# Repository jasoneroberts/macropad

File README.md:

# Macropad with a screen

A wireless macropad with MX keys, an EC11 knob and a small LCD that shows what each key does. It is built on the same nRF52840 / Zephyr / nRF Connect SDK stack as the [trackball](https://github.com/jasoneroberts/NordicMouseProject), with a 3D-printed case and a hand-soldered PCB. Started 2026-10-20.

Status 2026-10-21: concept B (12 keys, 2.0″ screen) and the SuperMini nRF52840 controller are chosen. The case model, firmware and PCB inputs exist for all three concepts; the firmware compiles but has not run on hardware yet, and nothing has been printed. Next: buy the screen and an EC11 knob and try the firmware on the nRF52840 DK.

Status 2026-11-11: the concept B main PCB is designed in full (schematic, placement, routing, ground pours) with its parts in a shared JR component library, ready to import into Altium 19 and order from JLCPCB: see `pcb/B/altium/README.md`. The controller pin map changed with it (LCD on footprint pins 5-10, rows 0/1 on P1.15/P0.02); the firmware and case follow.

| | A · Pocket | B · Studio (chosen) | C · Deck |
|---|---|---|---|
| Keys | 3 × 3 MX hot-swap | 4 × 3 MX hot-swap | 4 × 4 MX hot-swap |
| Knob (EC11) | Ø26 | Ø28 | Ø36 |
| Screen | 1.69″ ST7789V2 240 × 280, portrait | 2.0″ ST7789 320 × 240, landscape | 1.28″ GC9A01 240 × 240, round |
| Footprint on desk | 76 × 122 mm | 101 × 118 mm | 92 × 142 mm |
| Height front / rear | 12.5 / 25.1 mm | 12.5 / 24.6 mm | 12.5 / 29.5 mm |
| Tilt | 6° | 6° | 7° |
| LiPo | 603040 | 603040 | 803040 |

Heights are without the 10 mm rubber feet (add about 2 mm).

## Folder

| Path | What |
|---|---|
| `scad/macropad.scad` | The parametric model. Every dimension is a named parameter at the top. |
| `stl/<A,B,C>/print/` | `top`, `bottom`, `knob`, `clamp`, already oriented for the printer bed. |
| `stl/<A,B,C>/view/` | Every part and dummy component (PCB, switches, display, controller, battery) in the assembled position. Made by `tools/build.py`; not kept in git. |
| `stl/test_coupon.stl` | Print this first: switch holes 13.9 / 14.0 / 14.1 / 14.2 (1 to 4 dots) and two insert holes. |
| `dxf/pcb_outline_<c>.dxf` | Main PCB outline with MX centre holes (Ø4) and pillar holes (Ø2.2), for Altium. Plate-frame mm, origin at the case's front-left corner. |
| `build/report_<c>.json` | Dimensions and positions of everything, plus the fit-check result. |
| `build/viewer_<c>.glb` | Coloured assembly. Opens in Windows 3D Viewer. |
| `build/fitcheck.txt` | Overlap check between all parts. Should say `OK` for each concept. |
| `page/index.html` | The concept comparison page with 3D viewers. Made by `tools/make_page.py`; not kept in git. |
| `tools/` | `build.py` (STLs, DXF, report, fit check, GLB), `drawings.py` (plan and section SVGs), `make_page.py` + `page_template.html`, `build_firmware.sh` (Linux: installs NCS v3.3.0 and builds all six firmware variants; CI runs it too). |
| `firmware/` | Zephyr / NCS v3.3.0 app: keys, knob, LVGL screen, USB + Bluetooth HID. See `firmware/README.md`. |
| `firmware/prebuilt/` | Ready-to-flash concept B images: `macropad_B_promicro.uf2` and `macropad_B_dk.hex`. GitHub Actions also builds them on every firmware change (the run's "Artifacts"). |
| `pcb/` | The concept B board for Altium (`pcb/B/altium/`), its KiCad working copy and scripts (`pcb/B/kicad/`, `pcb/board/`), the shared JR component library (`pcb/library/`), and `generate.py`'s starting kits for all three concepts. See `pcb/README.md`. |
| `SHOPPING.md` | What to buy for B (UK prices) and what to measure when it arrives. |
| `LICENSES/` | Upstream licences for the files based on Nordic and Zephyr samples (see "Licences" below). |

## Rebuild after changing a parameter

Needs OpenSCAD 2021.01 or newer, Python 3 and `pip install trimesh manifold3d numpy scipy networkx`.

From the repo root:

```
python tools/build.py          # all concepts (or: build.py B)
python tools/drawings.py
python pcb/generate.py         # needs pip install shapely
python tools/make_page.py page
```

To export one part by hand: `openscad -D 'concept="B"' -D 'part="top_print"' -o top.stl scad/macropad.scad`. Open the file in the OpenSCAD GUI to use the Customizer for `concept` and `part`.

## Measure before printing

These come from listings or datasheets, not from parts on the bench:

- Display glass outline, thickness and where the active area sits on the glass (`LCD169`, `LCD200`, `GC9A01` tables). Board sizes and active areas are from Waveshare; glass outlines are estimates.
- EC11 body height above the PCB (`enc_body_h`, 6.5) and shaft length (`enc_shaft_l`, 15).
- Heat-set insert hole (`insert_d` 4.0, `insert_len` 4.0 for M3 × 4 short inserts).
- LiPo size (`LIPO_603040`, `LIPO_803040`).
- Switch hole (`sw_hole` 14.0): use the test coupon.

## How it's built

- Top shell = switch plate. 3 mm skin: 1.5 mm lip with the 14 mm hole, 15 mm pocket below for the MX clips. PCB top 5.0 mm below the plate top (MX standard), Kailh sockets under the PCB.
- The top surface is tilted, the bottom plate is flat, so the inside gets deeper toward the back. LiPo, controller and display stack live under the rear band.
- Display: window = active area + 0.4 mm with a 45° chamfer through a 1 mm bezel; glass in a pocket; printed clamp with two M2 screws holds the module board. Main PCB has a cut-out there; 8 wires to the module.
- Controller: SuperMini nRF52840 (chosen 2026-10-21; a nice!nano v2 also fits) on 2.5 mm headers under the PCB, component side down, USB-C (mid-mount, centred on the 1.6 mm module board) through a 13 × 7.5 mm rear opening.
- Four M3 countersunk screws into M3 heat-set inserts in the corner bosses; M2 self-tapping screws for the PCB pillars and the display clamp; slide switch slot in the right wall for the OS102011MA1QN1's actuator.
- Prints without supports: top shell face down, bottom plate and clamp flat, knob top face down. Largest part is C's top shell, 92 × 140 mm.

## Licences

No licence has been chosen for the project as a whole yet, so the default applies (all rights reserved). Two kinds of file keep their upstream licence, named by the `SPDX-License-Identifier` line at the top of the file:

- `firmware/src/BT.c` is based on Nordic's `peripheral_hids_keyboard` sample: `LicenseRef-Nordic-5-Clause` (`LICENSES/LicenseRef-Nordic-5-Clause.txt`), which allows use only with Nordic chips.
- `firmware/CMakeLists.txt` and `firmware/Kconfig` come from Zephyr's USB samples: Apache-2.0 (`LICENSES/Apache-2.0.txt`).

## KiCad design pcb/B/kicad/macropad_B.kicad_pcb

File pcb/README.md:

# Macropad main PCB

**Concept B is designed in full:** schematic, placement, routing and ground pours, ready for Altium 19 and a JLCPCB order. Start with [`B/altium/README.md`](B/altium/README.md). The parts come from the shared JR library in [`library/`](library/README.md).

| Folder | What it is |
|---|---|
| `B/altium/` | **The concept B design for Altium**: EAGLE import files, the guide, schematic and board PDFs, BOM, order list, reference Gerbers. |
| `B/kicad/` | The same board as a KiCad 7 project (the working copy the scripts build, route and check). |
| `board/` | The scripts that make it: `design_b.py` (parts, nets, pin map, placement), `build_board.py`, `route.py`, `schematic.py`, `export_altium.py`, `check.py`, `check_eagle.py`, `render.py`. |
| `library/` | The JR component library (symbols, footprints, part data), shared with the Gameball carrier. |
| `A/`, `B/`, `C/` | The earlier starting kits from `generate.py` (below): netlist, placement and outline, for drawing a board from scratch. Still generated for all three concepts; for B the full design above replaces them. |

## Starting kits (`generate.py`)

One folder per concept (`A/`, `B/`, `C/`), generated by `generate.py` from the case model, so the parts always match the printed case.

| File | What it is |
|---|---|
| `BOM.csv` | Every part with a UK price estimate. The last two rows (screen, LiPo) are off-board. |
| `connections.csv` | Net, designator, pin. Easiest way to check a connection by eye. |
| `macropad_<c>.NET` | Protel netlist. In Altium: create the PCB, then **Design > Import Changes From** / **Import Netlist**. |
| `placement.csv` | Position, side and rotation of every part, in mm. |
| `placement.svg` | The same as a drawing (top view, bottom-side parts seen through the board). |
| `pcb_outline.dxf` | Board outline with the MX centre holes, M2 pillar holes and the display opening. |

All coordinates use the case's frame: origin at the case's front-left corner, x to the right, y toward the back (the screen end). Import the DXF on a mechanical layer with that origin (**Edit > Origin > Set** on the DXF's 0,0) and the placement numbers line up.

Rebuild after changing the case, from the repo root: `python tools/build.py` then `python pcb/generate.py` (needs `pip install shapely`).

## Controller pin map

The controller is a SuperMini nRF52840 (chosen 2026-10-21), a clone of the nice!nano v2; a genuine nice!nano is a drop-in swap. Same table as `firmware/boards/promicro_nrf52840_nrf52840_uf2.overlay`, `generate.py` and `board/design_b.py`. Changed on 2026-11-11 so that pins 5-10 carry the LCD's six signals in the Waveshare cable order and run straight across to J2 on the board.

| Pin | Label | nRF52840 | Net | Why this pin |
|---|---|---|---|---|
| 1 | D1 | P0.06 | DBG_TX (TP1) | optional UART log |
| 2 | D0 | P0.08 | ROW3 (C only) | |
| 3, 4, 23 | GND | | GND | |
| 5 | D2 | P0.17 | LCD_MOSI (DIN) | full-speed pin, SPI data |
| 6 | D3 | P0.20 | LCD_SCK (CLK) | full-speed pin, SPI clock |
| 7 | D4 | P0.22 | LCD_CS | |
| 8 | D5 | P0.24 | LCD_DC | |
| 9 | D6 | P1.00 | LCD_RST | |
| 10 | D7 | P0.11 | LCD_BL (PWM) | normal-speed pin, 1 kHz PWM |
| 11 | D8 | P1.04 | ROW2 | |
| 12 | D9 | P1.06 | COL0 | |
| 13 | D10 | P0.09 | ENC_A | NFC pin, see below |
| 14 | D16 | P0.10 | ENC_B | NFC pin, see below |
| 15 | D14 | P1.11 | COL1 | |
| 16 | D15 | P1.13 | COL2 | |
| 17 | D18 | P1.15 | ROW0 | |
| 18 | D19 | P0.02 | ROW1 | |
| 19 | D20 | P0.29 | COL3 (A: knob push column) | |
| 20 | D21 | P0.31 | COL4 (B, C: knob push column) | |
| 21 | VCC | 3.3 V out | 3V3_SW (LCD power) | switched by P0.13, firmware turns it on |
| 22 | RST | nRESET | NRST (SW_RST) | |
| 24 | B+ | battery + | VBAT_SW (from SW_PWR) | |

Things that drove this map:

- **Nordic marks 21 pins "low frequency I/O only"** (keep them under about 10 kHz). On a Pro Micro footprint that is pins 11-20 (P1.04, P1.06, P0.09, P0.10, P1.11, P1.13, P1.15, P0.02, P0.29, P0.31). The 16 MHz LCD clock and data therefore sit on P0.20 and P0.17; the key matrix and knob are slow and can use the restricted pins.
- **P0.09 / P0.10 are the NFC antenna pins.** The board file already frees them as GPIO. They leak a little current between each other when held at different levels, so they carry the knob: both contacts are open (pulled high) at every detent.
- **The VCC pin is off until firmware drives P0.13 high** on SuperMini boards (it enables the regulator behind VCC). The firmware does this through a `regulator-fixed` node, so the LCD gets power before the display driver starts.

## Matrix

Rows are inputs with pull-ups, columns are driven low one at a time (Zephyr's `gpio-kbd-matrix`). Each switch goes from its row to a 1N4148W anode; the cathode goes to the column. Matrix row 0 is the back row, next to the screen; `SW1` is the back-left key, which is key 0 in the firmware and the top-left tile on screen. The knob's push switch is wired into row 0 in its own column (with its own diode), and the firmware calls it key 16 on every concept.

| Concept | Rows x columns | Knob push |
|---|---|---|
| A | 3 x 4 | row 0, COL3 |
| B | 3 x 5 | row 0, COL4 |
| C | 4 x 5 | row 0, COL4 |

## Assembly notes

- **U1 goes on the bottom layer, components facing down,** on 2.5 mm low-profile headers. Placing the standard Pro Micro footprint on the bottom layer in Altium mirrors it correctly. Keep the USB-C end toward the back wall (+y); the case has a 13 x 7.5 mm opening there.
- **On B and C the knob sits right above U1.** Trim the EC11's pins and mounting lugs flush under the board before fitting U1, and put a piece of Kapton tape on U1's back.
- **The space between the PCB top and the case skin is 2 mm.** Header pins and anything else poking up through the board must be trimmed flush.
- **LCD:** the Waveshare modules come with an 8-wire PH2.0 cable. Cut the far end and solder the wires into J2 in the module's order (VCC, GND, DIN, CLK, CS, DC, RST, BL). Leave enough slack to lift the module out of the window.
- **Power switch:** a right-angle SPDT slide switch on the bottom side, actuator out of the slot in the right wall. The part and its height are a best guess; check the actuator reaches through the 2.4 mm wall before ordering boards.
- **Reset button:** only needed if a firmware update goes wrong (double-press = UF2 bootloader). The firmware has a combo for normal updates: hold the top-left key and press the knob for 3 seconds.
- **SuperMini extras:** the three pins in the middle at the far end from USB (P1.01, P1.02, P1.07) are not used and need no header. The four SWD pads on its back (VDD, SWDIO, SWCLK, GND) are the way back in if the UF2 bootloader is ever damaged: the DK's Debug out header can reprogram it.
- **Charging speed:** the SuperMini charges at 100 mA, about 9 hours for a flat 800 mAh LiPo. Bridging the BOOST jumper on its back raises that to 300 mA (about 3 hours), which is fine for this cell but not for one under 500 mAh.
- **Placement check:** `generate.py` refuses to write files if two bottom-side parts overlap, a part leaves the board, or a part lands in the display opening. U1 under the knob is the one allowed overlap.

## Estimate (B)

About £9 of parts on the board (the £4.50 SuperMini is most of it), plus £11 for the screen and £6 for the LiPo: about £26, before switches, keycaps, the PCB itself and screws. See the shopping list in `../SHOPPING.md`.

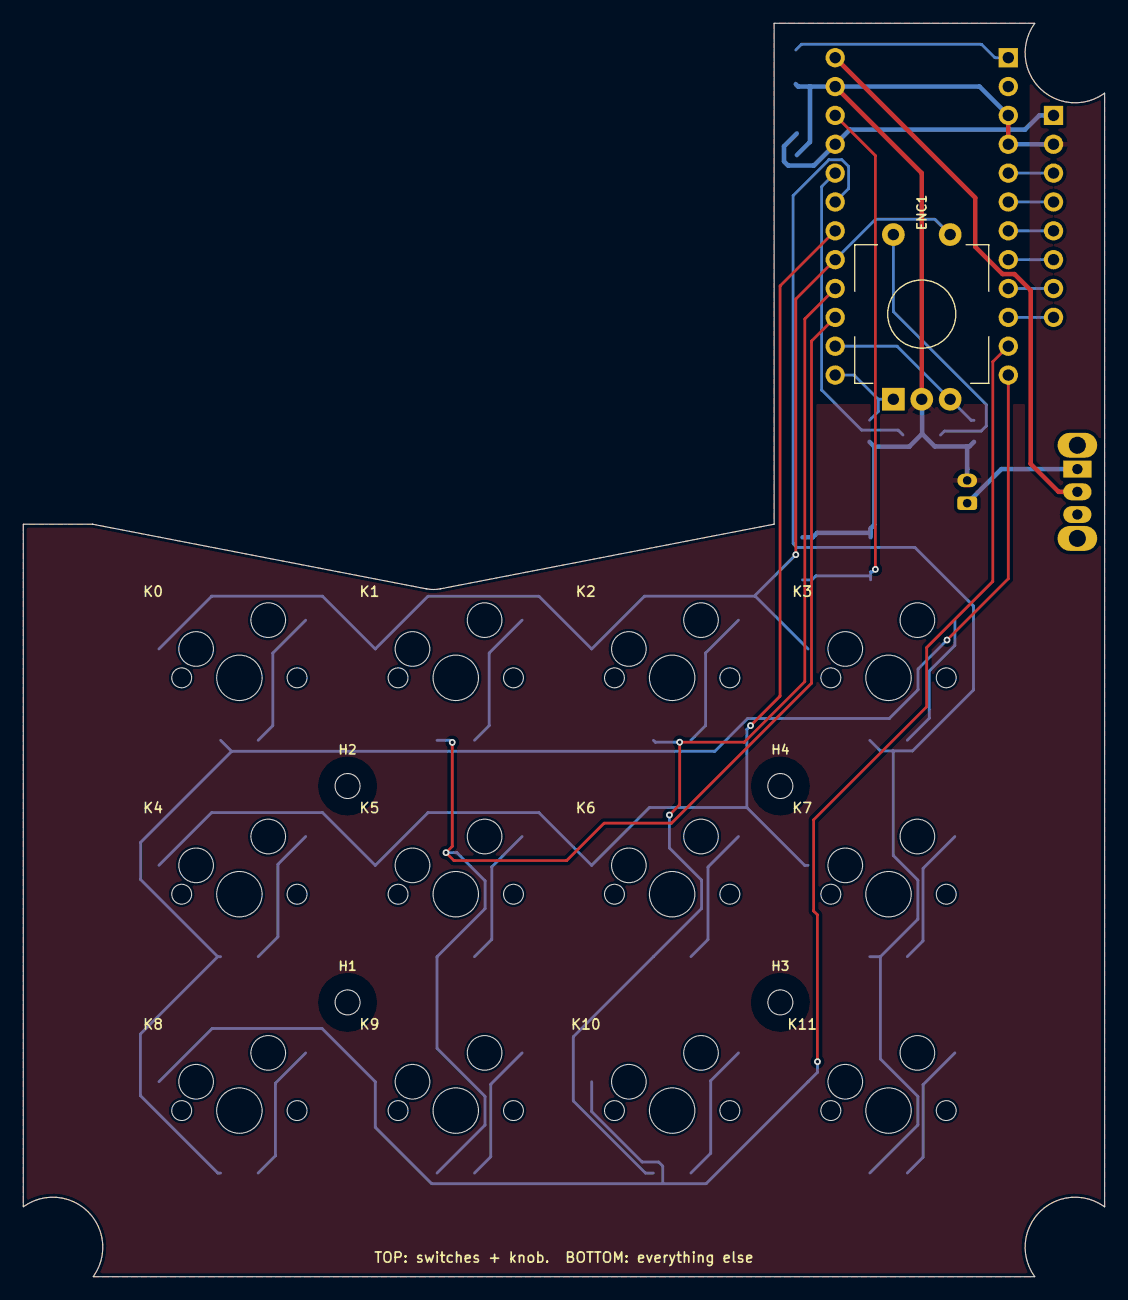
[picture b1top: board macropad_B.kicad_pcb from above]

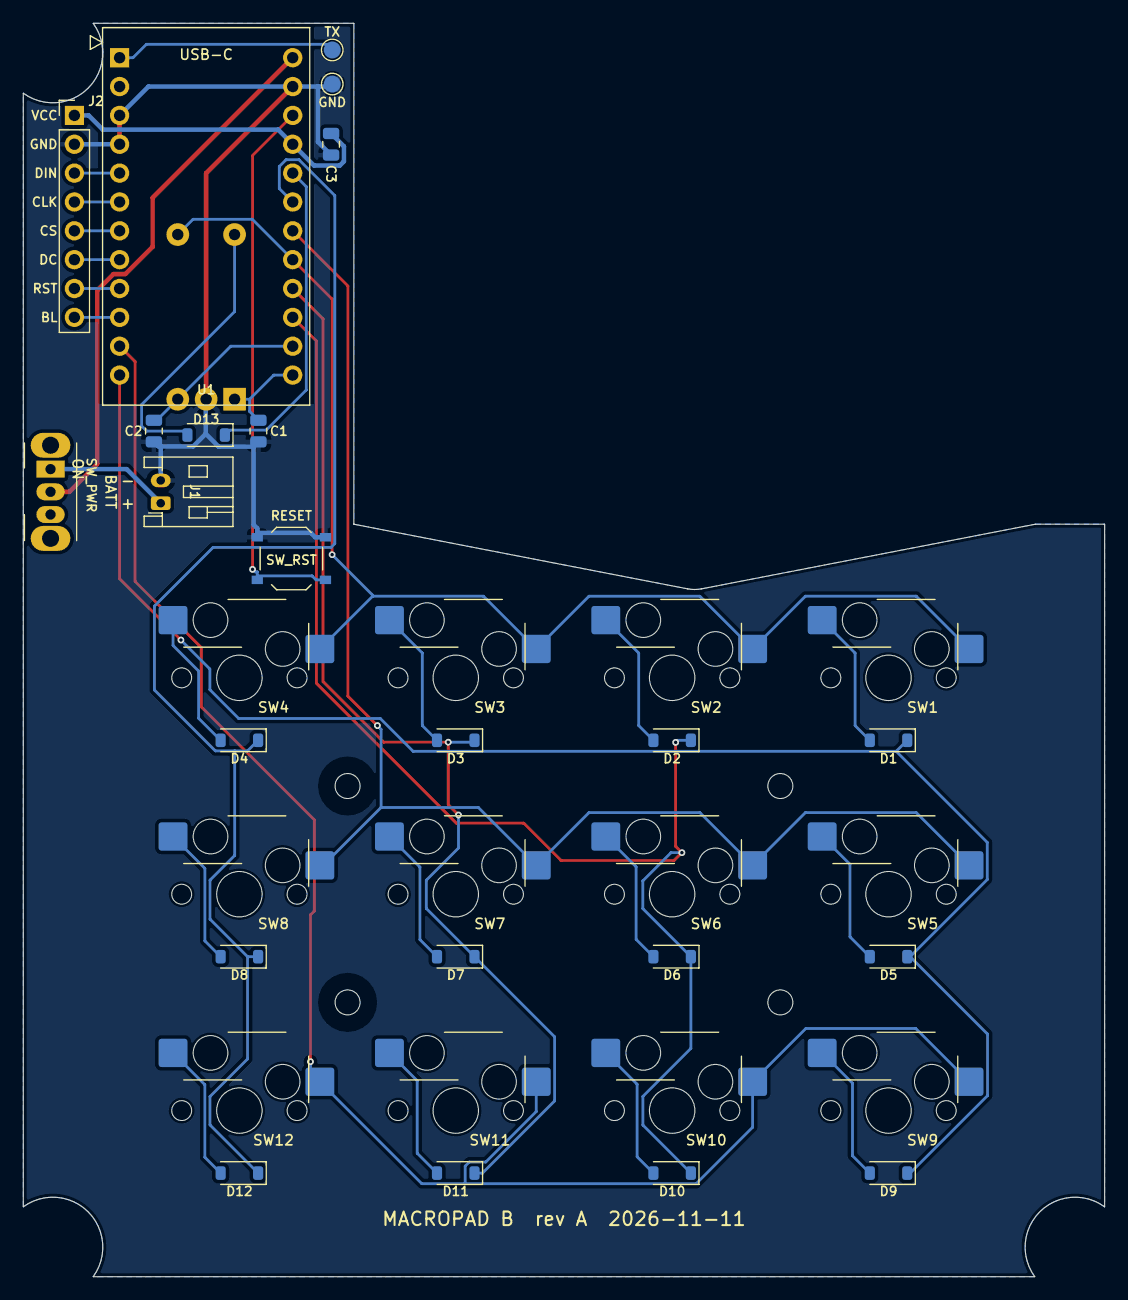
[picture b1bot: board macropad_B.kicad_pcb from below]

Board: 2 copper layers, 95.2 x 110.3 mm, 40 parts (35 on the bottom side), 35 nets.

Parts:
C1, C2: 10nF; C_0805_2012Metric
C3: 10uF; C_0805_2012Metric
D1, D2, D3, D4, D5, D6, D7, D8, D9, D10, D11, D12, D13: 1N4148W; D_SOD-123
ENC1: PEC11R-4220F-S0024; RotaryEncoder_EC11_Switch_NPTH
H1, H2, H3, H4: M2 hole; MountingHole_2.2mm_M2
J1: S2B-PH-K-S; JST_PH_S2B-PH-K_1x02_P2.00mm_Horizontal
J2: Wire pads 1x8; PinHeader_1x08_P2.54mm_Vertical
SW1, SW2, SW3, SW4, SW5, SW6, SW7, SW8, SW9, SW10, SW11, SW12: MX hot-swap; SW_Kailh_MX_Hotswap
SW_PWR: OS102011MA1QN1; SW_Slide_SPDT_Angled_CK_OS102011MA1Q
SW_RST: TS-1187A-B-A-B; SW_Push_1P1T_XKB_TS-1187A
TP1, TP2: Test pad; TestPoint_Pad_D1.5mm
U1: SuperMini nRF52840; SuperMini_nRF52840

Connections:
3V3_SW: C3.1, J2.1, U1.21
COL0: D1.1, D5.1, D9.1, U1.12
COL1: D2.1, D6.1, D10.1, U1.15
COL2: D3.1, D7.1, D11.1, U1.16
COL3: D4.1, D8.1, D12.1, U1.19
COL4: D13.1, U1.20
DBG_TX: TP1.1, U1.1
ENC_A: C1.1, ENC1.A, U1.13
ENC_B: C2.1, ENC1.B, U1.14
GND: C1.2, C2.2, C3.2, ENC1.C, J1.2, J2.2, SW_RST.3, SW_RST.4, TP2.1, U1.3, U1.4, U1.23
K1: D1.2, SW1.2
K2: D2.2, SW2.2
K3: D3.2, SW3.2
K4: D4.2, SW4.2
K5: D5.2, SW5.2
K6: D6.2, SW6.2
K7: D7.2, SW7.2
K8: D8.2, SW8.2
K9: D9.2, SW9.2
K10: D10.2, SW10.2
K11: D11.2, SW11.2
K12: D12.2, SW12.2
K_PUSH: D13.2, ENC1.S2
LCD_BL: J2.8, U1.10
LCD_CS: J2.5, U1.7
LCD_DC: J2.6, U1.8
LCD_MOSI: J2.3, U1.5
LCD_RST: J2.7, U1.9
LCD_SCK: J2.4, U1.6
NRST: SW_RST.1, SW_RST.2, U1.22
ROW0: ENC1.S1, SW1.1, SW2.1, SW3.1, SW4.1, U1.17
ROW1: SW5.1, SW6.1, SW7.1, SW8.1, U1.18
ROW2: SW9.1, SW10.1, SW11.1, SW12.1, U1.11
VBAT: J1.1, SW_PWR.1
VBAT_SW: SW_PWR.2, U1.24

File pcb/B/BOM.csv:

Designators,Qty,Value,Manufacturer,Manufacturer part number,Package,Est. unit GBP,Description
"C1, C2",2,10nF,,,0805,0.02,Encoder debounce (with the internal pull-up)
C3,1,10uF,,,0805,0.05,LCD supply bulk (backlight switch-on)
"D1, D2, D3, D4, D5, D6, D7, D8, D9, D10, D11, D12, D13",13,1N4148W,Diodes Inc,1N4148W-7-F,SOD-123,0.03,Matrix diode
ENC1,1,EC11 encoder with switch,Alps Alpine (or generic EC11),EC11E15244G1,"EC11, THT, 15-20 mm D-shaft",1.8,"Knob: volume, push = mute"
"H1, H2, H3, H4",4,M2 hole,,,2.2 mm NPTH,,M2 self-tapping screw into the case pillar
J1,1,Battery,JST,B2B-PH-K-S(LF)(SN),"JST PH 2-pin, THT, vertical",0.2,LiPo plug. Check the cell's lead polarity before plugging in
J2,1,LCD wires,,,"8 x 1.0 mm plated holes, 2.54 mm pitch",,Solder the module's cable here (Waveshare order)
"SW1, SW2, SW3, SW4, SW5, SW6, SW7, SW8, SW9, SW10, SW11, SW12",12,MX hot-swap socket,Kailh,CPG151101S11,MX hot-swap socket (pads on bottom),0.12,"Key socket, switch plugs in from the top"
SW_PWR,1,Power switch,generic,SK12D07VG4,"SPDT slide, right-angle THT, 2.54 mm",0.3,Battery on/off. Actuator pokes out of the right wall slot. MEASURE vs case slot
SW_RST,1,Reset,C&K,PTS636 SM25 SMTR LFS,"6 x 3.5 mm tact, gull-wing",0.25,Double-press = UF2 bootloader (case open)
TP1,1,DBG_TX,,,1.5 mm test pad,,"UART log out (115200), optional"
TP2,1,GND,,,1.5 mm test pad,,"UART log out (115200), optional"
U1,1,SuperMini nRF52840,generic (or nice!nano v2),nice!nano v2 compatible,"Pro Micro 24-pin DIP, 2.54 mm, rows 15.24 mm apart",4.5,"nRF52840 module with LiPo charger and USB-C. Bottom side, components facing down, on 2.5 mm low-profile headers; no headers on the 3 inner pins (P1.01, P1.02, P1.07)"
LCD,1,Waveshare 2inch LCD Module (ST7789V 240x320),Waveshare,,module,11.0,"Screen, sits in the case window"
BT1,1,"603040 LiPo 3.7 V ~800 mAh, JST-PH lead",,,pouch cell,6.0,"Under the display band, on the bottom plate"

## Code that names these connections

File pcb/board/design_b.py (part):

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    (24, "B+", "", "VBAT_SW"),
]
# Waveshare LCD cable order (VCC, GND, DIN, CLK, CS, DC, RST, BL)
J2_PINS = [(1, "VCC", "3V3_SW"), (2, "GND", "GND"), (3, "DIN", "LCD_MOSI"), (4, "CLK", "LCD_SCK"), (5, "CS", "LCD_CS"),
           (6, "DC", "LCD_DC"), (7, "RST", "LCD_RST"), (8, "BL", "LCD_BL")]

ROWS, COLS = REPORT["rows"], REPORT["cols"]          # 3 x 4 keys; the knob push is column 4
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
